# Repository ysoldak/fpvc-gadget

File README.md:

# FPV Combat Gadget

DIY device (gadget) that helps you quickly adjust [FPV Combat](https://www.fpv-combat.com) board settings like player ID, player name, lives, ammo and many more.

This is an alternative to classic way of using OSD menu (and IR remote earlier).  
It is a convenient way to adjust settings "on the go", at the field, for everyone.

FPV Combat board shall be flashed with compatible [firmware](https://github.com/FPV-Combat/Main_board_v2/releases).

**Gadget version 0.5.0+ requires FPV Combat version 2.8.0+.**

## Electronic Components

You'll need to buy some electronic components and 3D print the case, see below.  
Soldering skills required.

| Picture  | Item    | Comment | Price (per item)  |
| -------- | ------- | ------- | ------- |
|  | [XIAO-nRF52840 board](https://www.seeedstudio.com/Seeed-XIAO-BLE-nRF52840-p-5201.html) | With battery charger | [$9.90](https://www.seeedstudio.com/Seeed-XIAO-BLE-nRF52840-p-5201.html) |
|  | [HC-12 network module](https://www.hc01.com/goods/640e91920be12d0114404c95) | 433Mhz | $12 |
|  | [0.96inch display](https://www.az-delivery.de/en/products/0-96zolldisplay) | OLED 128 x 64 | [$2.4](https://www.alibaba.com/product-detail/Most-Popular-GME12864-White-4pins-I2C_1600270997819.html) - [$3.8](https://www.amazon.se/dp/B074NJMPYJ) |
|  | KY-040 rotary encoder | Breakout | [$1.8](https://www.amazon.se/dp/B07TKK4QQD) |
|  | [Adafruit TLV62569 (4711)](https://www.adafruit.com/product/4711) | Step-down converter 3.4~5.5V to 3.3V | [$3.95](https://www.digikey.se/sv/products/detail/adafruit-industries-llc/4711/13162412) |
|  | Prototype board | 30 x 70 mm, or PCB | [$0.8](https://www.amazon.se/dp/B07CQQK214) |
|  | LiPo Battery | 1S, 100-500mAh, 45 x 25 x 9 mm | [$11](https://www.amazon.se/dp/B01FBSA1N6/) |
|  | Micro Slide Switch | 2 positions, 3 contacts | [$0.1](https://www.amazon.se/Gebildet-Vertikal-Switch-SS-12d00-Position/dp/B08L6FMV84/?th=1) | 
| **Total** ||| **$45** |

### Alternatives
- MCU
  - [XIAO-RP2040](https://www.seeedstudio.com/XIAO-RP2040-v1-0-p-5026.html) - $5.40 (cheaper, no battery charger)
  - [XIAO-nRF52840 Sense](https://www.seeedstudio.com/Seeed-XIAO-BLE-Sense-nRF52840-p-5253.html) - $15.99 (more expensive, has IMU that we don't use)
- Step-down converter
  - [LM3671](https://www.adafruit.com/product/2745) - $4.95
  - [TPS62827](https://www.adafruit.com/product/4920) - $6.95
  - [DFR0568](https://www.dfrobot.com/product-1765.html) - $2.9
- Battery charger (optional, use with MCU w/o built-in battery charger)
  - [Greluma 6st](https://www.amazon.se/dp/B09WMVLWH5)

## Assembly

It is possible to [order the gadget](https://www.etsy.com/se-en/listing/1589030767/fpv-combat-gadget-battery-not-included) either fully assembled, as a kit or just PCB from [our shop on Etsy](https://www.etsy.com/se-en/shop/SkyGadgets).

Alternatively, you can always order PCB yourself from PCBWay, JLCPCB and alike or use 30x70mm prototype board.

### Assembly tips

- Once soldered, backs of pins/slots have to be filed out/flattened, otherwise risk of damaging the battery;
- Straighten encoder pins and cut them a bit, just a several mm;
- Cut a bit of encoder pcb, across mounting holes, otherwise it does not fit;
- HC-12 is placed white (flat) side up;
- Pull HC-12 antenna a little so it is away from everything to minimise interference.

### Schematic

### PCB

## Contacts

Join our [FPV-Combat Community](https://www.facebook.com/groups/2441262976051510/)

Questions? [Make an issue](https://github.com/ysoldak/fpvc-gadget/issues) on this repository or search Yurii Soldak in our FB group.

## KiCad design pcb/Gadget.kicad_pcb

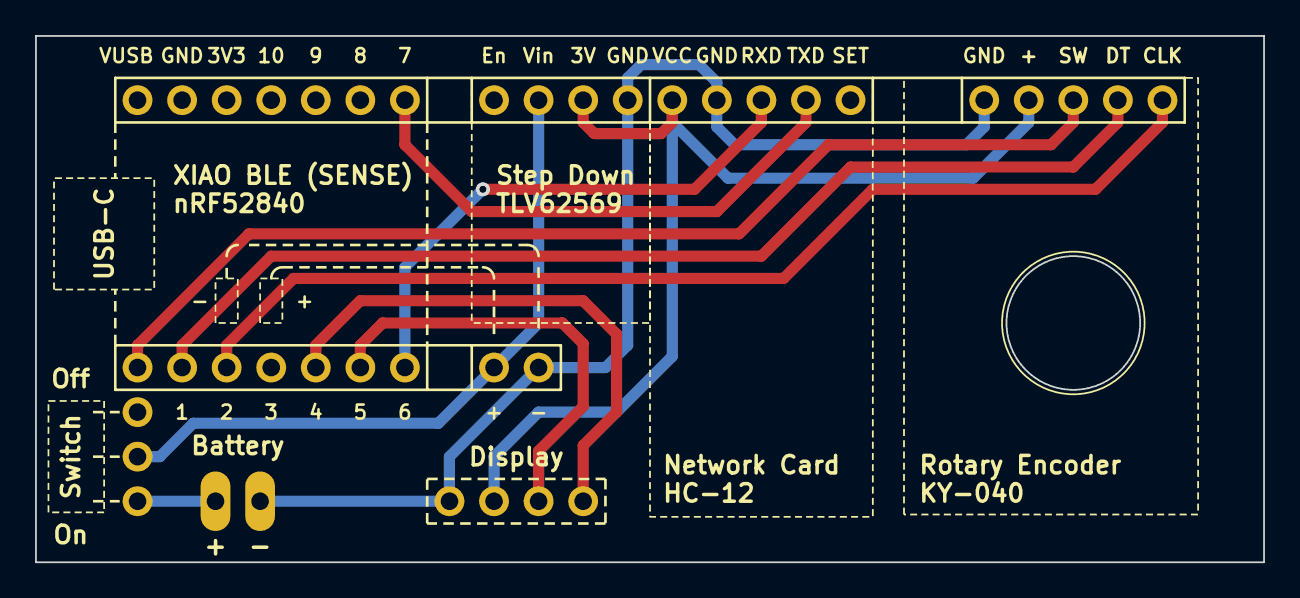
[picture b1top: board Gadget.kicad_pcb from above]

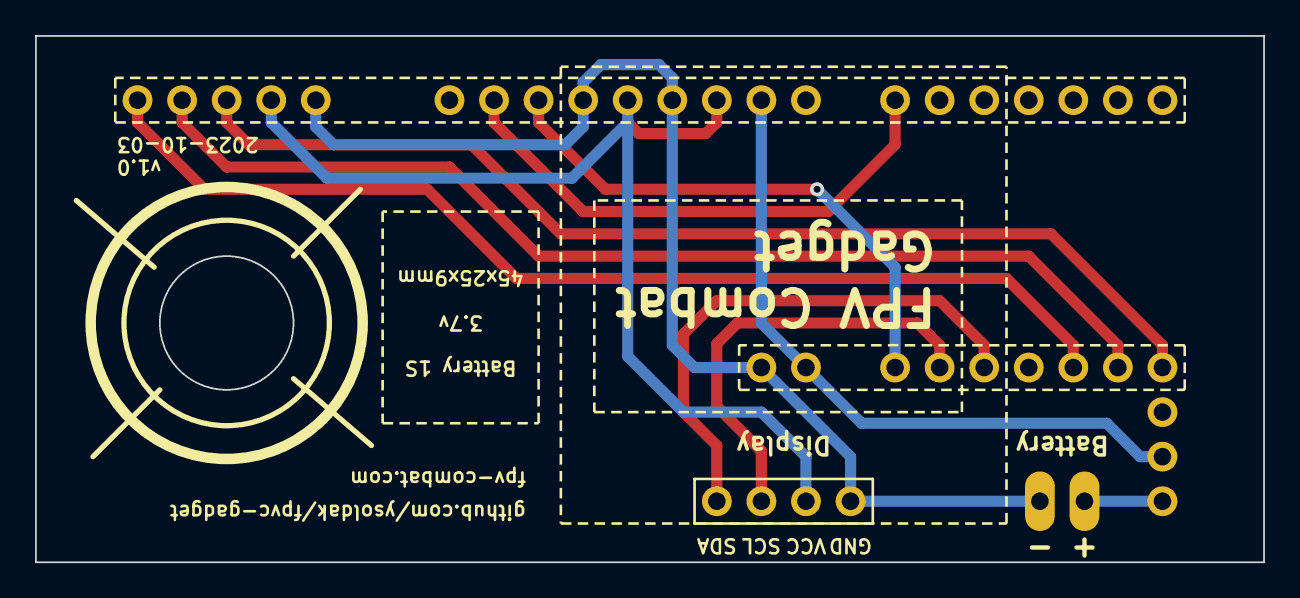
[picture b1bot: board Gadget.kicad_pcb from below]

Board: 2 copper layers, 70.0 x 30.0 mm, 7 parts (2 on the bottom side), 11 nets.

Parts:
BT1: Battery_Cell; Battery Connector
SW1: SW_SPST; Switch
U1: SeeeduinoXIAO nRF52840; XIAO-NRF52840
U2: KY-040; RotaryEncoder KY-040
U3: Display 128x64; Display 0.96 128x64
U4: HC-12
U5: TLV62569

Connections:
+3.3V: U2.2 (+), U3.2 (VCC), U4.1 (VCC), U5.3 (3V)
-BATT: BT1.2 (-), U1.16 (BAT-), U2.1 (GND), U3.1 (GND), U4.2 (GND), U5.4 (GND)
unnamed: BT1.1 (+), SW1.1 (A)
unnamed: SW1.2 (B), U1.15 (BAT+), U5.2 (Vin)
unnamed: U1.1 (PA02_A0_D0), U2.3 (SW)
unnamed: U1.2 (PA4_A1_D1), U2.4 (DT)
unnamed: U1.5 (PA8_A4_D4_SDA), U3.4 (SDA)
unnamed: U1.6 (PA9_A5_D5_SCL), U3.3 (SCL)
unnamed: U1.3 (PA10_A2_D2), U2.5 (CLK)
unnamed: U1.7 (PB08_A6_D6_TX), U4.3 (RXD)
unnamed: U1.8 (PB09_A7_D7_RX), U4.4 (TXD)

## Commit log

2023-08-08 First working version with limited functionality
2023-08-08 cleanup
2023-08-15 Can set single bytes
2023-08-15 Can change team
2023-08-15 Click debounce
2023-08-15 Can set name
2023-08-15 Clean old data with rectangle
2023-08-15 Filter invalid values
2023-08-15 Ignore settings
2023-08-16 Improve settings presentation
2023-08-17 Display error set indication better
2023-08-17 Implement settings scroll
2023-09-15 More params
2023-09-15 Bill of materials
2023-09-15 Customisable target
2023-09-27 Prepare for release
2023-09-27 Minor fixes
2023-09-27 Fix worflow step name
2023-10-01 Show battery voltage on start
2023-10-03 PCB design
2023-10-03 PCB design (#6)
2023-10-04 pcb change after output
2023-10-16 Adjust case to match PCB
2023-10-16 Adjust case to match PCB (#7)
2023-10-16 Update README.md
    - Removed link to bad Amazon item
    - Added links to some items
    - Added link to Etsy shop (order gadget, kit or PCB)
2023-10-16 Update README.md
    - Link to OLED display description
2023-10-16 Assembly tips
2023-10-30 Set cursor at first device setting on open
2023-10-30 Can go back even after config fetch failure
2023-10-30 Addr Led renamed to Team Led
2023-10-30 Show device description Also: - UI elemnts positions adjusted a bit - Wrap cursor up and down - Ignore invalid device IDs and re-try
2023-10-30 Assorted mini fixes (#8)
    Device page: cursor is at first device setting on page open
    Device page: can go back even after config fetch failure
    Device page: "Addr Led" renamed to "Team Led"
    Device page: show device description (contains just firmware version as of FW 2.5.0)
    Device page: wrap cursor up and down
    Scan page: Ignore invalid device IDs during scan
2024-01-02 Bump dependencies and TinyGo version
2024-01-02 Read out all before requesting config
2024-01-02 Fix scan screen initial cursor
2024-01-16 New knob, prints better with 0.4mm nozzle and 95% flow
2024-02-25 make: flash-release
2024-02-25 Sync with FPVCombat 2.6.0
2024-02-25 Update case STLs
2024-03-13 bare minimum
2024-03-15 support almost all settings
2024-03-15 support upcoming 2.7 firmware plus fix for increment
2024-03-15 Support FPV Combat 2.6.X and 2.7.X (#10)
    * bare minimum
    * support almost all settings
    * support upcoming 2.7 firmware
    plus fix for increment
2024-05-12 Cleanup unsupported HW 2.5 pin settings + some renames CSP stands for Combat Serial Protocol FC is Flight Controller AU is Air Unit (digital VTX)
2024-05-12 Cleanup unsupported HW 2.5 pin settings + some renames (#11)
    CSP stands for Combat Serial Protocol
    FC is Flight Controller
    AU is Air Unit (digital VTX)
2024-07-05 device: set player number
2024-07-05 CSP protocol update
2024-07-06 CSP fixes
2024-07-07 Assorted CSP fixes
2024-07-07 CSP Protocol Update (#13)
    * device: set player number
    * CSP protocol update
    * CSP fixes
    * Assorted CSP fixes
2024-07-08 Use CSP library
2024-07-08 Gadget pic
2024-07-08 Gadget Loves You
2024-07-08 Bump CSP lib to v1.1.1
2025-06-03 Support MSP AU on HW25
    Also:
    - Fixes ports configuration on HW26
    - Adds Settings address constants
2025-06-03 Bump versions in workflows
2025-06-03 Initialize ADC in Battery configuration
2025-06-04 Support MSP AU on HW25 (#14)
    * Support MSP AU on HW25
    Also:
    - Fixes ports configuration on HW26
    - Adds Settings address constants
    * Bump versions in workflows
    * Initialize ADC in Battery configuration
2025-12-11 Support HW27
2025-12-11 flash-release uses latest tag
2025-12-28 Bump TinyGo to 0.40.1
2025-12-28 Support HW27 + use TinyGo 0.40.1 (#15)
